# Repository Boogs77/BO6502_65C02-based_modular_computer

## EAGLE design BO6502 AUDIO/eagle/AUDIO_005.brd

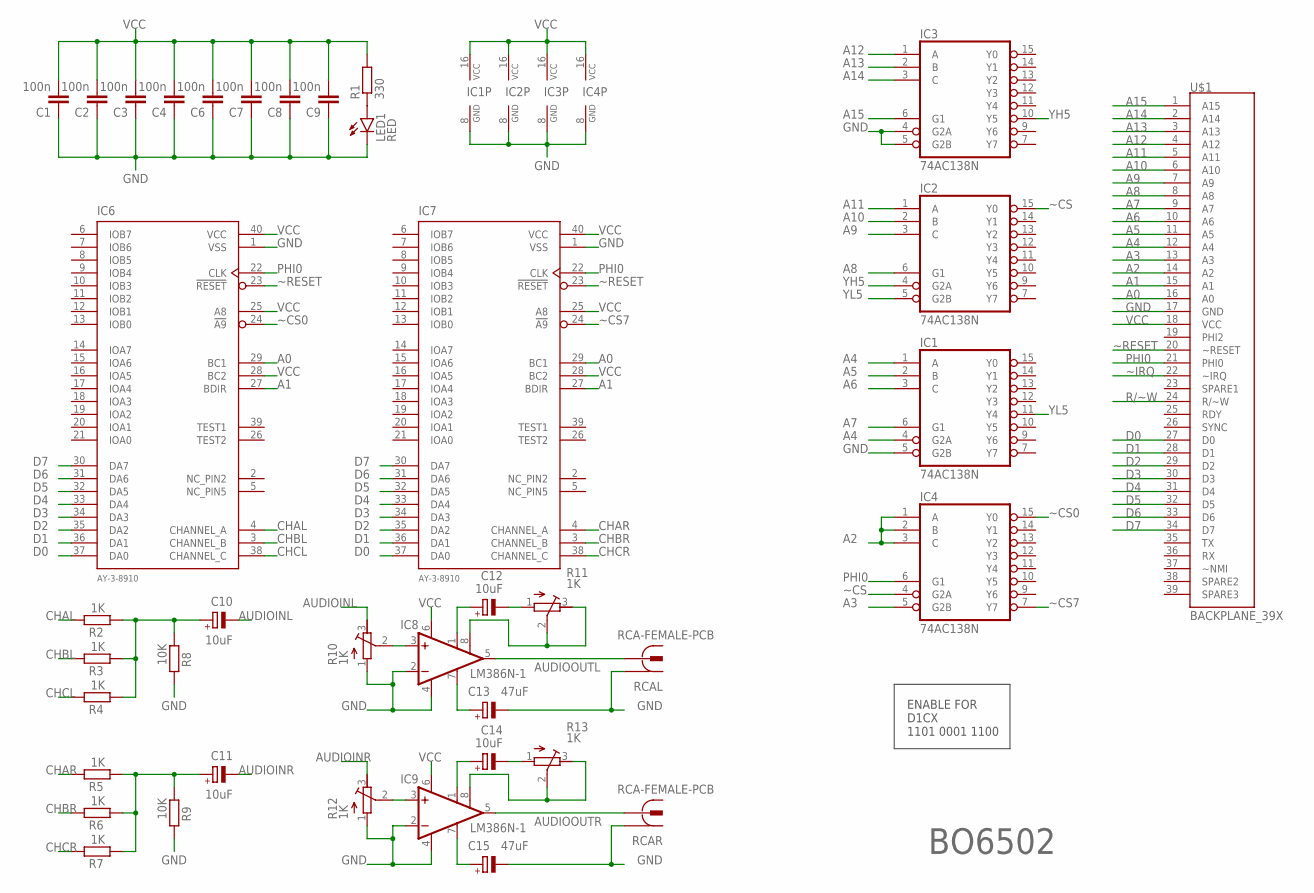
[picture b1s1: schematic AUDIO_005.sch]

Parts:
C1, C2, C3, C4, C6, C7, C8, C9: 100n; C025-025X050
C10, C11, C12, C14: 10uF; B45181A
C13, C15: 47uF; B45181A
IC1, IC2, IC3, IC4: 74AC138N; DIL16
IC6, IC7: AY-3-8910; DIL40
IC8, IC9: LM386N-1; DIL08
LED1: RED; LED5MM
R1: 330; 0207/10
R2, R3, R4, R5, R6, R7: 1K; 0207/10
R8, R9: 10K; 0207/10
R10, R11, R12, R13: 1K; RTRIM3339P
RCAL: RCA-FEMALE-PCB
RCAR: RCA-FEMALE-PCB
U$1: BACKPLANE_39X; BP_39X

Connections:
A0: IC6.29 (BC1), IC7.29 (BC1), U$1.16 (A0)
A1: IC6.27 (BDIR), IC7.27 (BDIR), U$1.15 (A1)
A2: IC4.1 (A), IC4.2 (B), IC4.3 (C), U$1.14 (A2)
A3: IC4.5 (G2B), U$1.13 (A3)
A4: IC1.1 (A), IC1.4 (G2A), U$1.12 (A4)
A5: IC1.2 (B), U$1.11 (A5)
A6: IC1.3 (C), U$1.10 (A6)
A7: IC1.6 (G1), U$1.9 (A7)
A8: IC2.6 (G1), U$1.8 (A8)
A9: IC2.3 (C), U$1.7 (A9)
A10: IC2.2 (B), U$1.6 (A10)
A11: IC2.1 (A), U$1.5 (A11)
A12: IC3.1 (A), U$1.4 (A12)
A13: IC3.2 (B), U$1.3 (A13)
A14: IC3.3 (C), U$1.2 (A14)
A15: IC3.6 (G1), U$1.1 (A15)
AUDIOINL: C10.-, R10.3 (E)
AUDIOINR: C11.-, R12.3 (E)
AUDIOOUTL: IC8.5 (OUT), RCAL.2@1 (2), RCAL.2@2 (2)
AUDIOOUTR: IC9.5 (OUT), RCAR.2@1 (2), RCAR.2@2 (2)
CHAL: IC6.4 (CHANNEL_A), R2.1
CHAR: IC7.4 (CHANNEL_A), R5.1
CHBL: IC6.3 (CHANNEL_B), R3.1
CHBR: IC7.3 (CHANNEL_B), R6.1
CHCL: IC6.38 (CHANNEL_C), R4.1
CHCR: IC7.38 (CHANNEL_C), R7.1
D0: IC6.37 (DA0), IC7.37 (DA0), U$1.27 (D0)
D1: IC6.36 (DA1), IC7.36 (DA1), U$1.28 (D1)
D2: IC6.35 (DA2), IC7.35 (DA2), U$1.29 (D2)
D3: IC6.34 (DA3), IC7.34 (DA3), U$1.30 (D3)
D4: IC6.33 (DA4), IC7.33 (DA4), U$1.31 (D4)
D5: IC6.32 (DA5), IC7.32 (DA5), U$1.32 (D5)
D6: IC6.31 (DA6), IC7.31 (DA6), U$1.33 (D6)
D7: IC6.30 (DA7), IC7.30 (DA7), U$1.34 (D7)
GND: C1.1, C2.1, C3.1, C4.1, C6.1, C7.1, C8.1, C9.1, C13.-, C15.-, IC1.5 (G2B), IC1.8 (GND), IC2.8 (GND), IC3.4 (G2A), IC3.5 (G2B), IC3.8 (GND), IC4.8 (GND), IC6.1 (VSS), IC7.1 (VSS), IC8.2 (-IN), IC8.4 (GND), IC9.2 (-IN), IC9.4 (GND), LED1.K (C), R8.1, R9.1, R10.1 (A), R12.1 (A), RCAL.1, RCAR.1, U$1.17 (GND)
unnamed: C10.+, R2.2, R3.2, R4.2, R8.2
unnamed: C12.+, IC8.1 (GAIN)
unnamed: IC8.3 (+IN), R10.2 (S)
unnamed: LED1.A, R1.1
unnamed: C12.-, R11.1 (A)
unnamed: IC8.8 (GAIN), R11.2 (S), R11.3 (E)
unnamed: C13.+, IC8.7 (BYPASS)
unnamed: IC9.3 (+IN), R12.2 (S)
unnamed: C14.+, IC9.1 (GAIN)
unnamed: C14.-, R13.1 (A)
unnamed: IC9.8 (GAIN), R13.2 (S), R13.3 (E)
unnamed: C15.+, IC9.7 (BYPASS)
unnamed: C11.+, R5.2, R6.2, R7.2, R9.2
PHI0: IC4.6 (G1), IC6.22 (CLK), IC7.22 (CLK), U$1.21 (PHI0)
R/~W: U$1.24 (R/~W)
VCC: C1.2, C2.2, C3.2, C4.2, C6.2, C7.2, C8.2, C9.2, IC1.16 (VCC), IC2.16 (VCC), IC3.16 (VCC), IC4.16 (VCC), IC6.25 (A8), IC6.28 (BC2), IC6.40 (VCC), IC7.25 (A8), IC7.28 (BC2), IC7.40 (VCC), IC8.6 (VS), IC9.6 (VS), R1.2, U$1.18 (VCC)
YH5: IC2.4 (G2A), IC3.10 (Y5)
YL5: IC1.11 (Y4), IC2.5 (G2B)
~CS: IC2.15 (Y0), IC4.4 (G2A)
~CS0: IC4.15 (Y0), IC6.24 (!A9)
~CS7: IC4.7 (Y7), IC7.24 (!A9)
~IRQ: U$1.22 (~IRQ)
~RESET: IC6.23 (!RESET), IC7.23 (!RESET), U$1.20 (~RESET)

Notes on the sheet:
BO6502
ENABLE FOR D1CX 1101 0001 1100

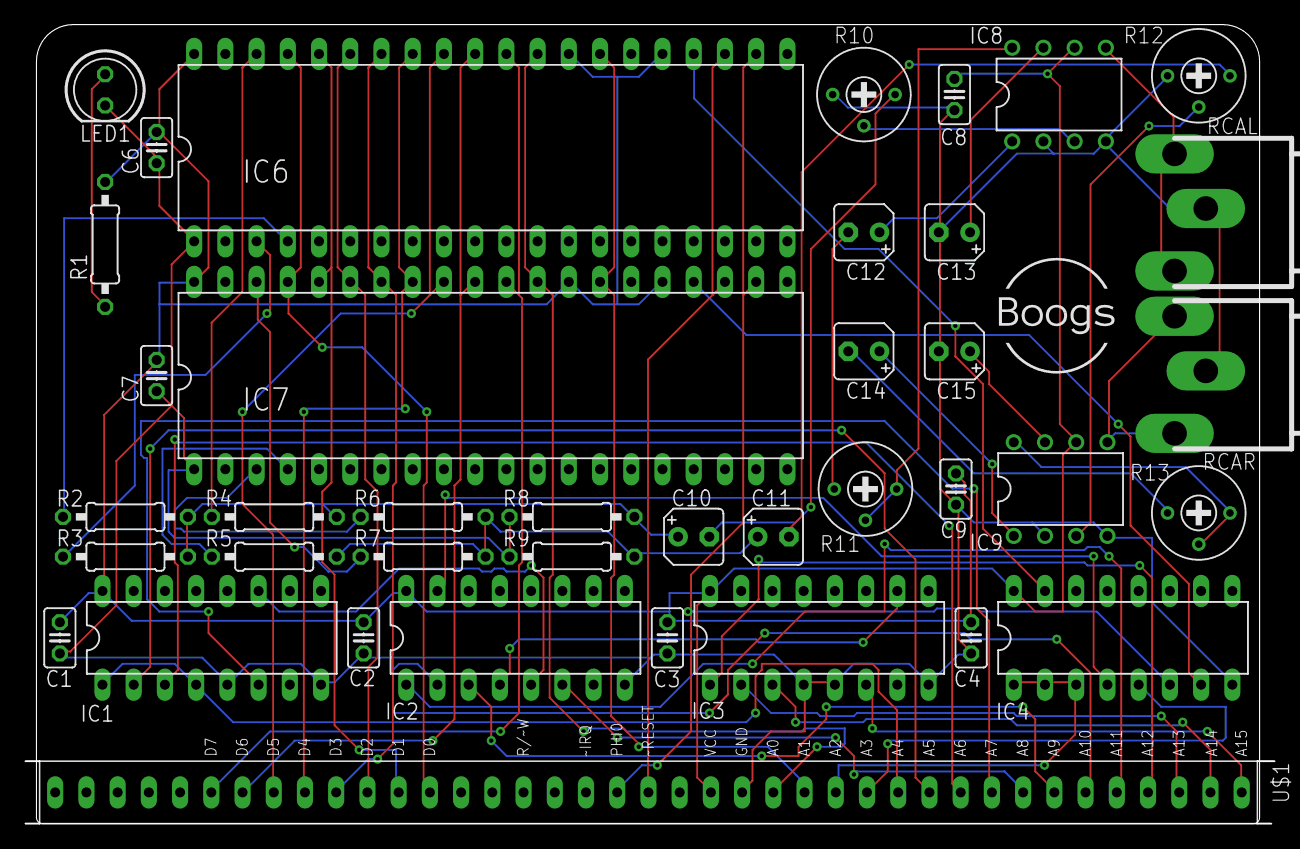
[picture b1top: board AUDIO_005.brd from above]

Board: 2 copper layers, 101.6 x 65.0 mm, 39 parts (0 on the bottom side), 56 nets.

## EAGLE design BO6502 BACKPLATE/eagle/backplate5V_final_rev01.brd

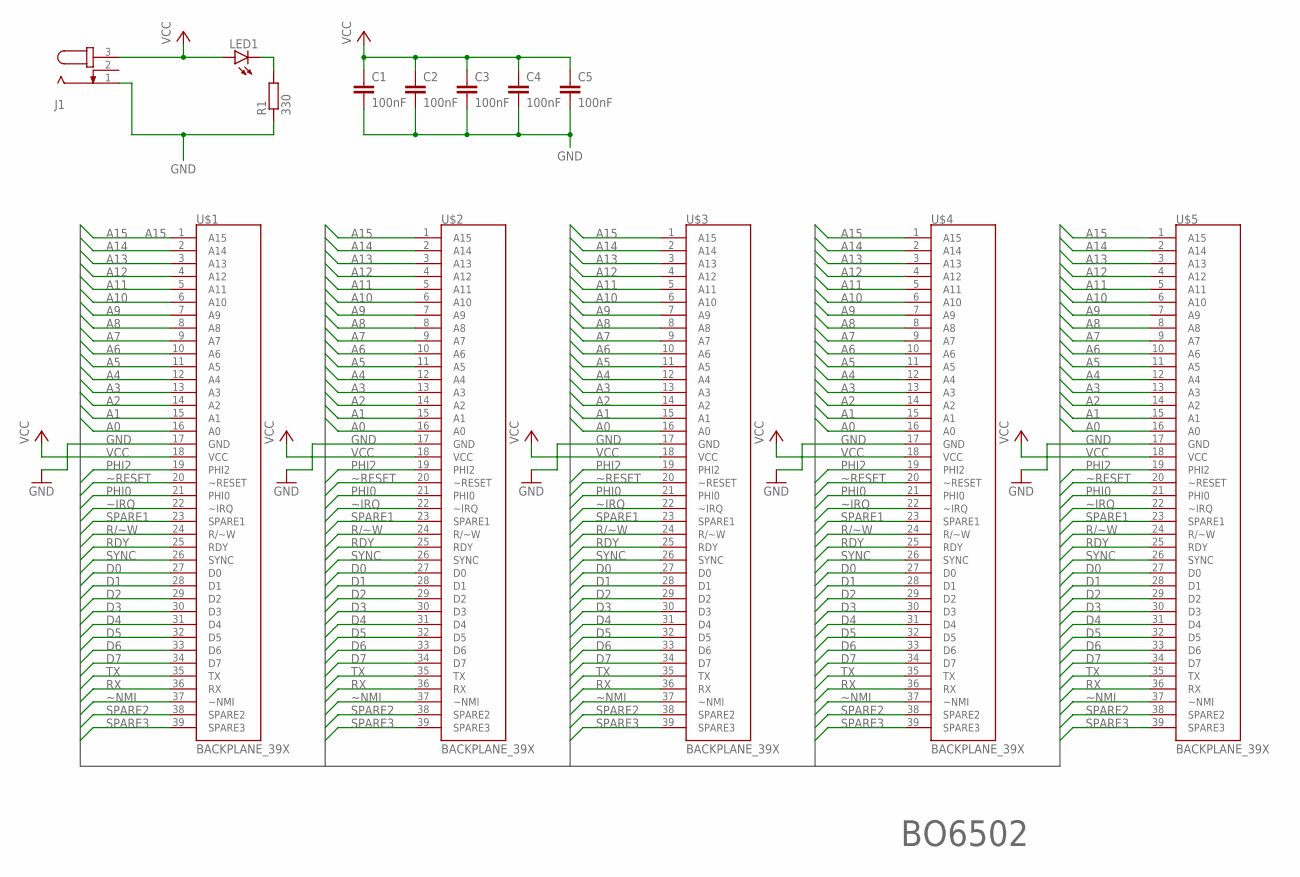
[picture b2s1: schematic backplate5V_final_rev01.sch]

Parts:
C1, C2, C3, C4, C5: 100nF; C025-025X050
J1: JACK-PLUG1; SPC4078
LED1: LED5MM
R1: 330; 0207/10
U$1, U$2, U$3, U$4, U$5: BACKPLANE_39X; BP_39X

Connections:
A0: U$1.16 (A0), U$2.16 (A0), U$3.16 (A0), U$4.16 (A0), U$5.16 (A0)
A1: U$1.15 (A1), U$2.15 (A1), U$3.15 (A1), U$4.15 (A1), U$5.15 (A1)
A2: U$1.14 (A2), U$2.14 (A2), U$3.14 (A2), U$4.14 (A2), U$5.14 (A2)
A3: U$1.13 (A3), U$2.13 (A3), U$3.13 (A3), U$4.13 (A3), U$5.13 (A3)
A4: U$1.12 (A4), U$2.12 (A4), U$3.12 (A4), U$4.12 (A4), U$5.12 (A4)
A5: U$1.11 (A5), U$2.11 (A5), U$3.11 (A5), U$4.11 (A5), U$5.11 (A5)
A6: U$1.10 (A6), U$2.10 (A6), U$3.10 (A6), U$4.10 (A6), U$5.10 (A6)
A7: U$1.9 (A7), U$2.9 (A7), U$3.9 (A7), U$4.9 (A7), U$5.9 (A7)
A8: U$1.8 (A8), U$2.8 (A8), U$3.8 (A8), U$4.8 (A8), U$5.8 (A8)
A9: U$1.7 (A9), U$2.7 (A9), U$3.7 (A9), U$4.7 (A9), U$5.7 (A9)
A10: U$1.6 (A10), U$2.6 (A10), U$3.6 (A10), U$4.6 (A10), U$5.6 (A10)
A11: U$1.5 (A11), U$2.5 (A11), U$3.5 (A11), U$4.5 (A11), U$5.5 (A11)
A12: U$1.4 (A12), U$2.4 (A12), U$3.4 (A12), U$4.4 (A12), U$5.4 (A12)
A13: U$1.3 (A13), U$2.3 (A13), U$3.3 (A13), U$4.3 (A13), U$5.3 (A13)
A14: U$1.2 (A14), U$2.2 (A14), U$3.2 (A14), U$4.2 (A14), U$5.2 (A14)
A15: U$1.1 (A15), U$2.1 (A15), U$3.1 (A15), U$4.1 (A15), U$5.1 (A15)
D0: U$1.27 (D0), U$2.27 (D0), U$3.27 (D0), U$4.27 (D0), U$5.27 (D0)
D1: U$1.28 (D1), U$2.28 (D1), U$3.28 (D1), U$4.28 (D1), U$5.28 (D1)
D2: U$1.29 (D2), U$2.29 (D2), U$3.29 (D2), U$4.29 (D2), U$5.29 (D2)
D3: U$1.30 (D3), U$2.30 (D3), U$3.30 (D3), U$4.30 (D3), U$5.30 (D3)
D4: U$1.31 (D4), U$2.31 (D4), U$3.31 (D4), U$4.31 (D4), U$5.31 (D4)
D5: U$1.32 (D5), U$2.32 (D5), U$3.32 (D5), U$4.32 (D5), U$5.32 (D5)
D6: U$1.33 (D6), U$2.33 (D6), U$3.33 (D6), U$4.33 (D6), U$5.33 (D6)
D7: U$1.34 (D7), U$2.34 (D7), U$3.34 (D7), U$4.34 (D7), U$5.34 (D7)
GND: C1.2, C2.2, C3.2, C4.2, C5.2, J1.1, R1.1, U$1.17 (GND), U$2.17 (GND), U$3.17 (GND), U$4.17 (GND), U$5.17 (GND)
unnamed: LED1.K (C), R1.2
PHI0: U$1.21 (PHI0), U$2.21 (PHI0), U$3.21 (PHI0), U$4.21 (PHI0), U$5.21 (PHI0)
PHI2: U$1.19 (PHI2), U$2.19 (PHI2), U$3.19 (PHI2), U$4.19 (PHI2), U$5.19 (PHI2)
R/~W: U$1.24 (R/~W), U$2.24 (R/~W), U$3.24 (R/~W), U$4.24 (R/~W), U$5.24 (R/~W)
RDY: U$1.25 (RDY), U$2.25 (RDY), U$3.25 (RDY), U$4.25 (RDY), U$5.25 (RDY)
RX: U$1.36 (RX), U$2.36 (RX), U$3.36 (RX), U$4.36 (RX), U$5.36 (RX)
SPARE1: U$1.23 (SPARE1), U$2.23 (SPARE1), U$3.23 (SPARE1), U$4.23 (SPARE1), U$5.23 (SPARE1)
SPARE2: U$1.38 (SPARE2), U$2.38 (SPARE2), U$3.38 (SPARE2), U$4.38 (SPARE2), U$5.38 (SPARE2)
SPARE3: U$1.39 (SPARE3), U$2.39 (SPARE3), U$3.39 (SPARE3), U$4.39 (SPARE3), U$5.39 (SPARE3)
SYNC: U$1.26 (SYNC), U$2.26 (SYNC), U$3.26 (SYNC), U$4.26 (SYNC), U$5.26 (SYNC)
TX: U$1.35 (TX), U$2.35 (TX), U$3.35 (TX), U$4.35 (TX), U$5.35 (TX)
VCC: C1.1, C2.1, C3.1, C4.1, C5.1, J1.3, LED1.A, U$1.18 (VCC), U$2.18 (VCC), U$3.18 (VCC), U$4.18 (VCC), U$5.18 (VCC)
~IRQ: U$1.22 (~IRQ), U$2.22 (~IRQ), U$3.22 (~IRQ), U$4.22 (~IRQ), U$5.22 (~IRQ)
~NMI: U$1.37 (~NMI), U$2.37 (~NMI), U$3.37 (~NMI), U$4.37 (~NMI), U$5.37 (~NMI)
~RESET: U$1.20 (~RESET), U$2.20 (~RESET), U$3.20 (~RESET), U$4.20 (~RESET), U$5.20 (~RESET)

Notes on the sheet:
BO6502

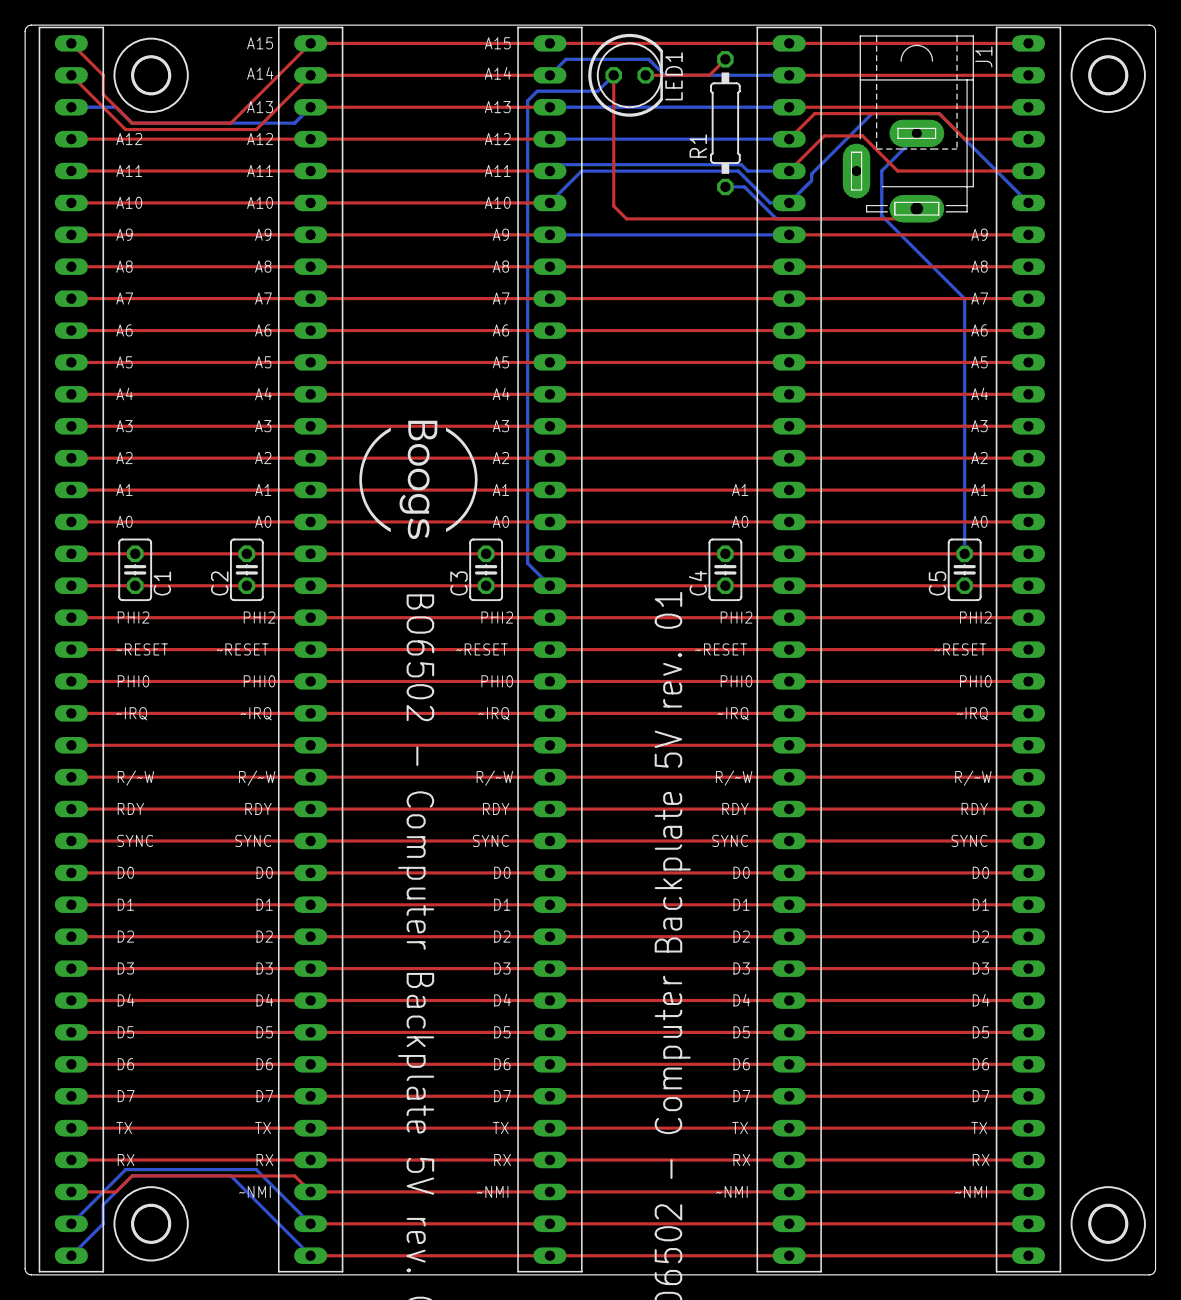
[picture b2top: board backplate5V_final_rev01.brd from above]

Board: 2 copper layers, 90.0 x 99.5 mm, 17 parts (0 on the bottom side), 40 nets.

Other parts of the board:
U$7, U$8, U$9, U$10: 2,8

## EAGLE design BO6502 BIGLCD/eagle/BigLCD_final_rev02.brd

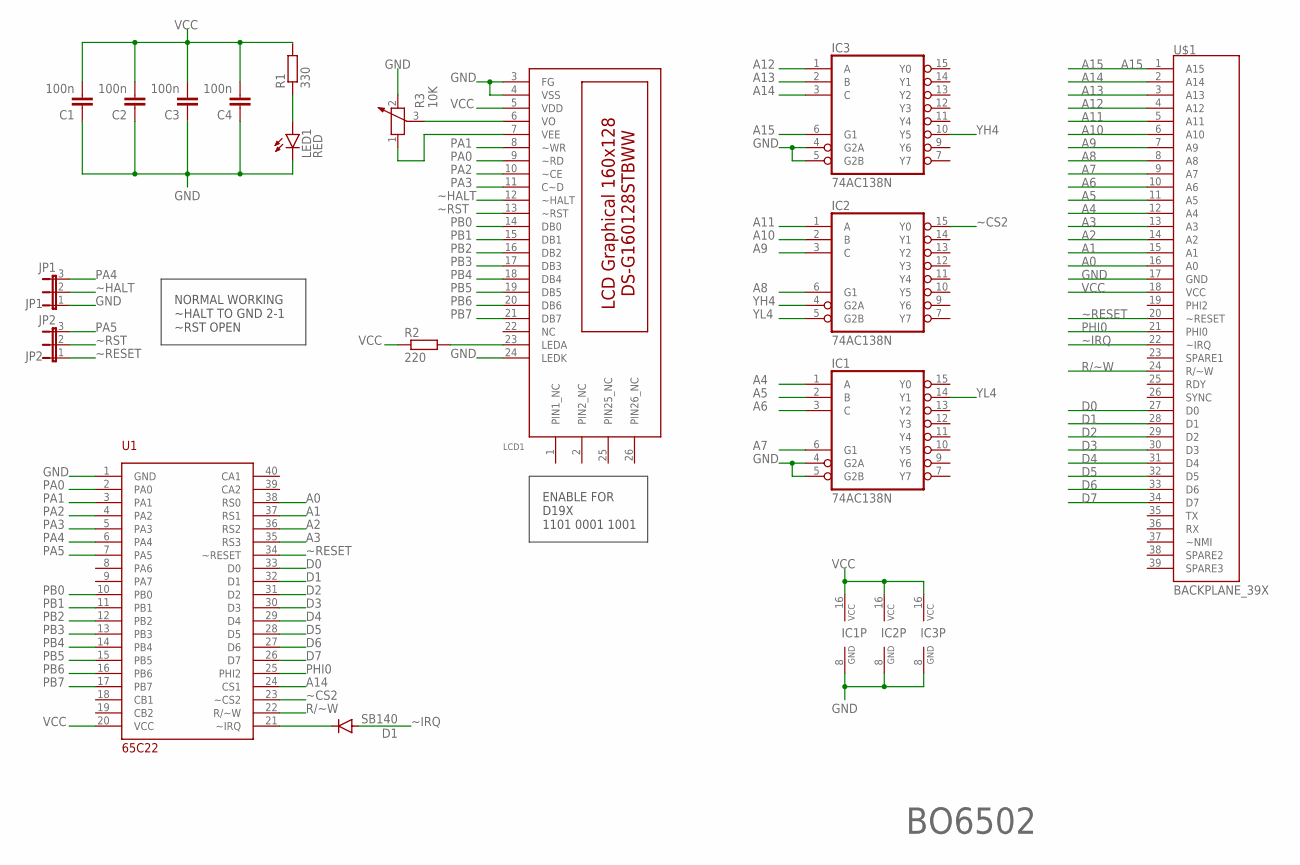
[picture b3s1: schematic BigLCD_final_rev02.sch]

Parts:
C1, C2, C3, C4: 100n; C025-025X050
D1: SB140; DO41-10
IC1, IC2, IC3: 74AC138N; DIL16
JP1: JP1; JP2
JP2: JP2
LCD1: DS-G160128STBWW; PAK100/2500-26
LED1: RED; LED5MM
R1: 330; 0207/10
R2: 220; 0207/10
R3: 10K; PT-10
U1: 65C22; DIL40
U$1: BACKPLANE_39X; BP_39X

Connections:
A0: U1.38 (RS0), U$1.16 (A0)
A1: U1.37 (RS1), U$1.15 (A1)
A2: U1.36 (RS2), U$1.14 (A2)
A3: U1.35 (RS3), U$1.13 (A3)
A4: IC1.1 (A), U$1.12 (A4)
A5: IC1.2 (B), U$1.11 (A5)
A6: IC1.3 (C), U$1.10 (A6)
A7: IC1.6 (G1), U$1.9 (A7)
A8: IC2.6 (G1), U$1.8 (A8)
A9: IC2.3 (C), U$1.7 (A9)
A10: IC2.2 (B), U$1.6 (A10)
A11: IC2.1 (A), U$1.5 (A11)
A12: IC3.1 (A), U$1.4 (A12)
A13: IC3.2 (B), U$1.3 (A13)
A14: IC3.3 (C), U1.24 (CS1), U$1.2 (A14)
A15: IC3.6 (G1), U$1.1 (A15)
D0: U1.33 (D0), U$1.27 (D0)
D1: U1.32 (D1), U$1.28 (D1)
D2: U1.31 (D2), U$1.29 (D2)
D3: U1.30 (D3), U$1.30 (D3)
D4: U1.29 (D4), U$1.31 (D4)
D5: U1.28 (D5), U$1.32 (D5)
D6: U1.27 (D6), U$1.33 (D6)
D7: U1.26 (D7), U$1.34 (D7)
GND: C1.1, C2.1, C3.1, C4.1, IC1.4 (G2A), IC1.5 (G2B), IC1.8 (GND), IC2.8 (GND), IC3.4 (G2A), IC3.5 (G2B), IC3.8 (GND), JP1.1, LCD1.3 (FG), LCD1.4 (VSS), LCD1.24 (LEDK), LED1.K (C), R3.2, U1.1 (GND), U$1.17 (GND)
unnamed: D1.C, U1.21 (~IRQ)
unnamed: LCD1.6 (VO), R3.3
unnamed: LCD1.7 (VEE), R3.1
unnamed: LCD1.23 (LEDA), R2.2
unnamed: LED1.A, R1.1
PA0: LCD1.9 (~RD), U1.2 (PA0)
PA1: LCD1.8 (~WR), U1.3 (PA1)
PA2: LCD1.10 (~CE), U1.4 (PA2)
PA3: LCD1.11 (C~D), U1.5 (PA3)
PA4: JP1.3, U1.6 (PA4)
PA5: JP2.3, U1.7 (PA5)
PB0: LCD1.14 (DB0), U1.10 (PB0)
PB1: LCD1.15 (DB1), U1.11 (PB1)
PB2: LCD1.16 (DB2), U1.12 (PB2)
PB3: LCD1.17 (DB3), U1.13 (PB3)
PB4: LCD1.18 (DB4), U1.14 (PB4)
PB5: LCD1.19 (DB5), U1.15 (PB5)
PB6: LCD1.20 (DB6), U1.16 (PB6)
PB7: LCD1.21 (DB7), U1.17 (PB7)
PHI0: U1.25 (PHI2), U$1.21 (PHI0)
R/~W: U1.22 (R/~W), U$1.24 (R/~W)
VCC: C1.2, C2.2, C3.2, C4.2, IC1.16 (VCC), IC2.16 (VCC), IC3.16 (VCC), LCD1.5 (VDD), R1.2, R2.1, U1.20 (VCC), U$1.18 (VCC)
YH4: IC2.4 (G2A), IC3.10 (Y5)
YL4: IC1.14 (Y1), IC2.5 (G2B)
~CS2: IC2.15 (Y0), U1.23 (~CS2)
~HALT: JP1.2, LCD1.12 (~HALT)
~IRQ: D1.A, U$1.22 (~IRQ)
~RESET: JP2.1, U1.34 (~RESET), U$1.20 (~RESET)
~RST: JP2.2, LCD1.13 (~RST)

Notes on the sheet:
BO6502
ENABLE FOR D19X 1101 0001 1001
NORMAL WORKING ~HALT TO GND 2-1 ~RST OPEN

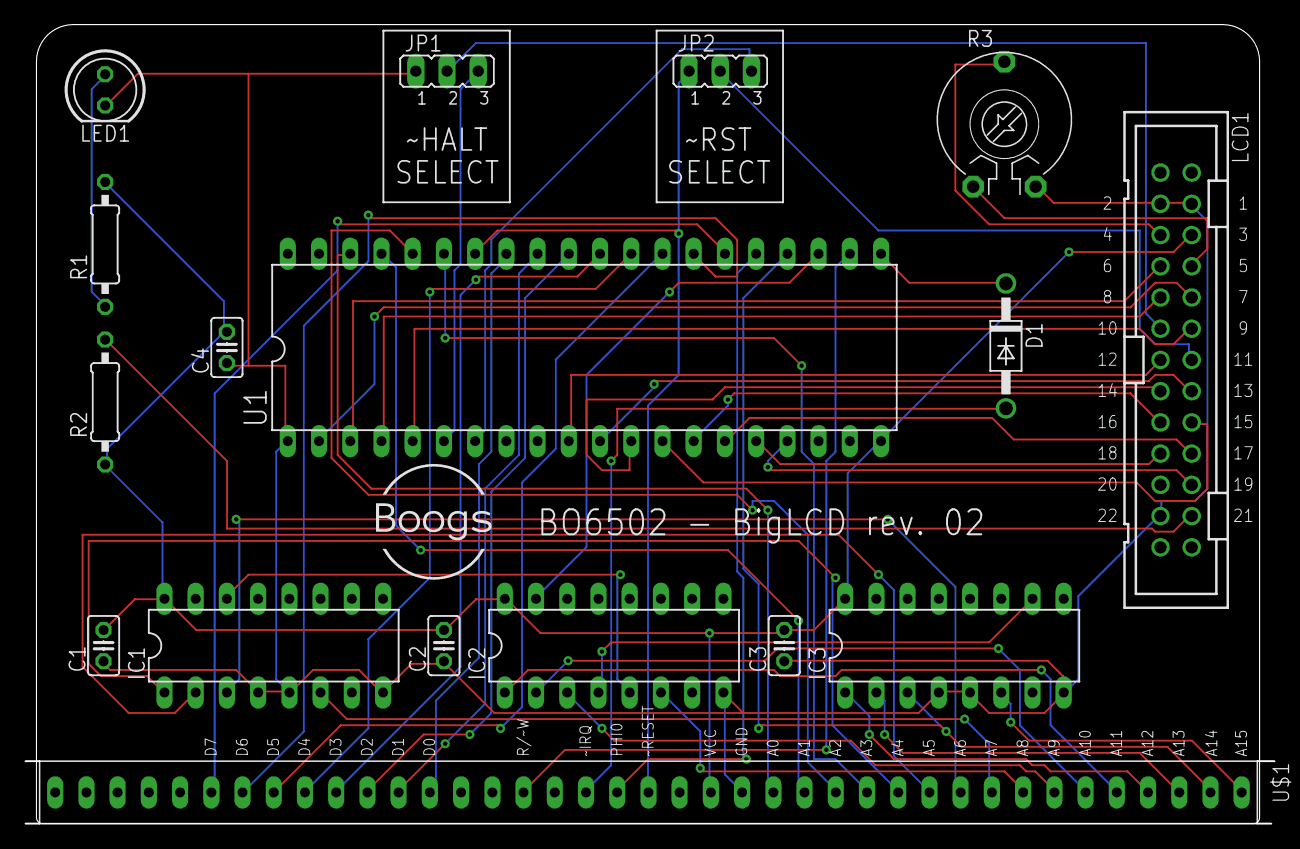
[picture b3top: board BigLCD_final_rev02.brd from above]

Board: 2 copper layers, 101.6 x 65.0 mm, 17 parts (0 on the bottom side), 54 nets.

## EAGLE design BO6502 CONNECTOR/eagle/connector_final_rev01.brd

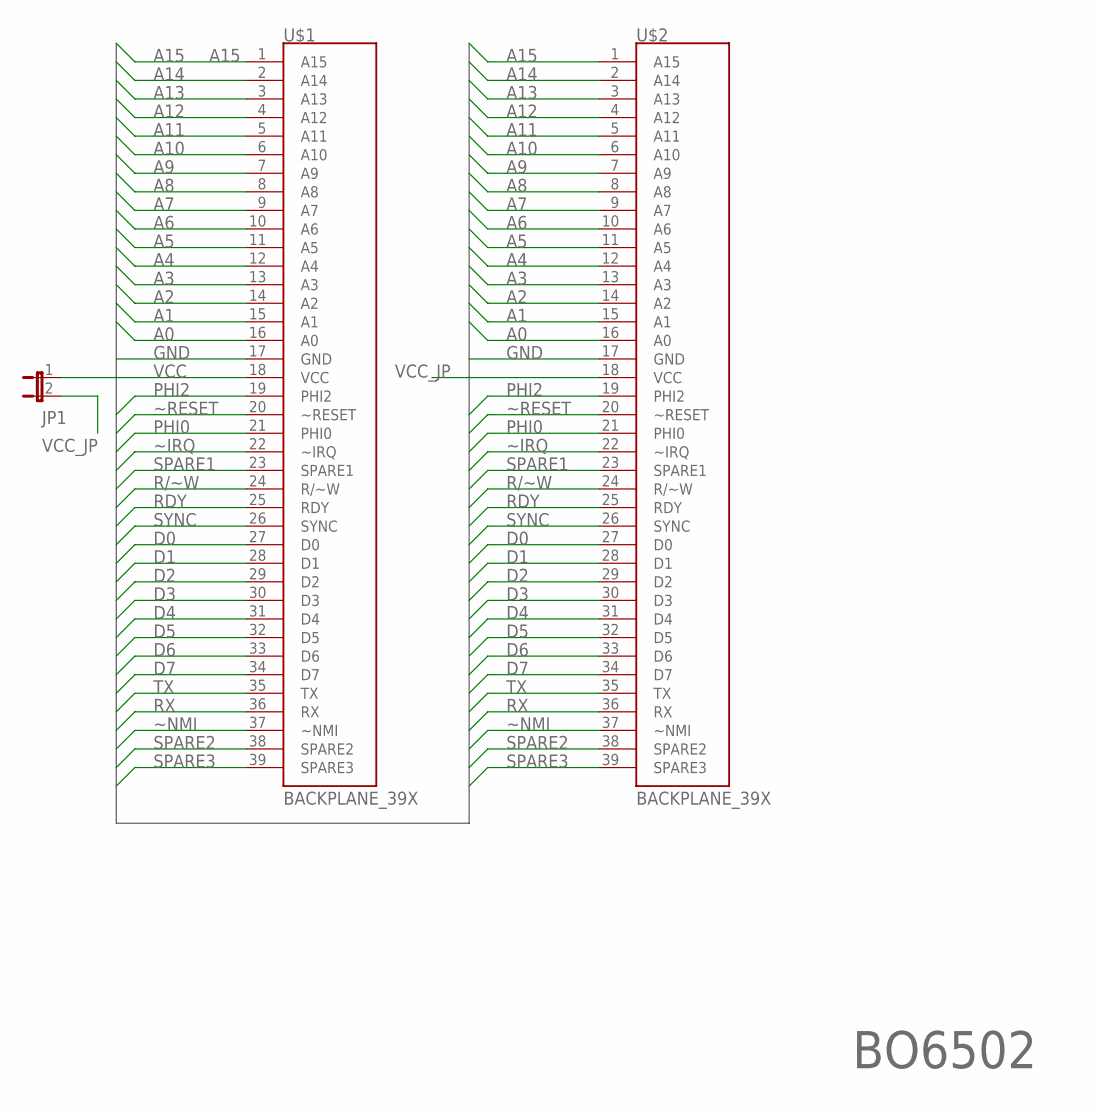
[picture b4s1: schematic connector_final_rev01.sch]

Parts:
JP1: JP1E; JP1
U$1, U$2: BACKPLANE_39X; BP_39X

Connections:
A0: U$1.16 (A0), U$2.16 (A0)
A1: U$1.15 (A1), U$2.15 (A1)
A2: U$1.14 (A2), U$2.14 (A2)
A3: U$1.13 (A3), U$2.13 (A3)
A4: U$1.12 (A4), U$2.12 (A4)
A5: U$1.11 (A5), U$2.11 (A5)
A6: U$1.10 (A6), U$2.10 (A6)
A7: U$1.9 (A7), U$2.9 (A7)
A8: U$1.8 (A8), U$2.8 (A8)
A9: U$1.7 (A9), U$2.7 (A9)
A10: U$1.6 (A10), U$2.6 (A10)
A11: U$1.5 (A11), U$2.5 (A11)
A12: U$1.4 (A12), U$2.4 (A12)
A13: U$1.3 (A13), U$2.3 (A13)
A14: U$1.2 (A14), U$2.2 (A14)
A15: U$1.1 (A15), U$2.1 (A15)
D0: U$1.27 (D0), U$2.27 (D0)
D1: U$1.28 (D1), U$2.28 (D1)
D2: U$1.29 (D2), U$2.29 (D2)
D3: U$1.30 (D3), U$2.30 (D3)
D4: U$1.31 (D4), U$2.31 (D4)
D5: U$1.32 (D5), U$2.32 (D5)
D6: U$1.33 (D6), U$2.33 (D6)
D7: U$1.34 (D7), U$2.34 (D7)
GND: U$1.17 (GND), U$2.17 (GND)
PHI0: U$1.21 (PHI0), U$2.21 (PHI0)
PHI2: U$1.19 (PHI2), U$2.19 (PHI2)
R/~W: U$1.24 (R/~W), U$2.24 (R/~W)
RDY: U$1.25 (RDY), U$2.25 (RDY)
RX: U$1.36 (RX), U$2.36 (RX)
SPARE1: U$1.23 (SPARE1), U$2.23 (SPARE1)
SPARE2: U$1.38 (SPARE2), U$2.38 (SPARE2)
SPARE3: U$1.39 (SPARE3), U$2.39 (SPARE3)
SYNC: U$1.26 (SYNC), U$2.26 (SYNC)
TX: U$1.35 (TX), U$2.35 (TX)
VCC: JP1.1, U$1.18 (VCC)
VCC_JP: JP1.2, U$2.18 (VCC)
~IRQ: U$1.22 (~IRQ), U$2.22 (~IRQ)
~NMI: U$1.37 (~NMI), U$2.37 (~NMI)
~RESET: U$1.20 (~RESET), U$2.20 (~RESET)

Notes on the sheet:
BO6502

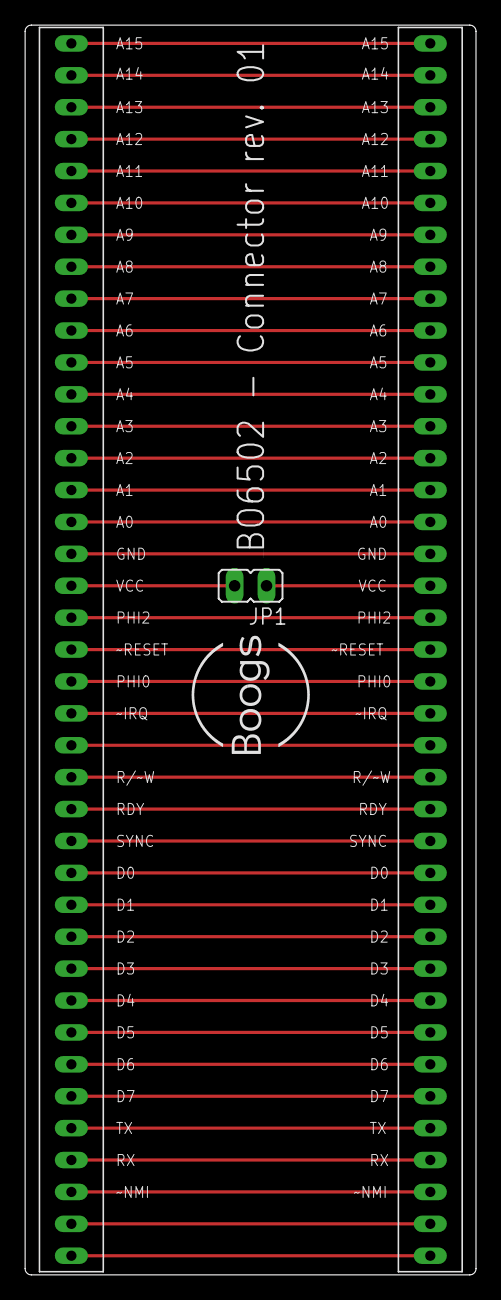
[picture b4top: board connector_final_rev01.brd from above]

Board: 2 copper layers, 35.9 x 99.5 mm, 3 parts (0 on the bottom side), 40 nets.

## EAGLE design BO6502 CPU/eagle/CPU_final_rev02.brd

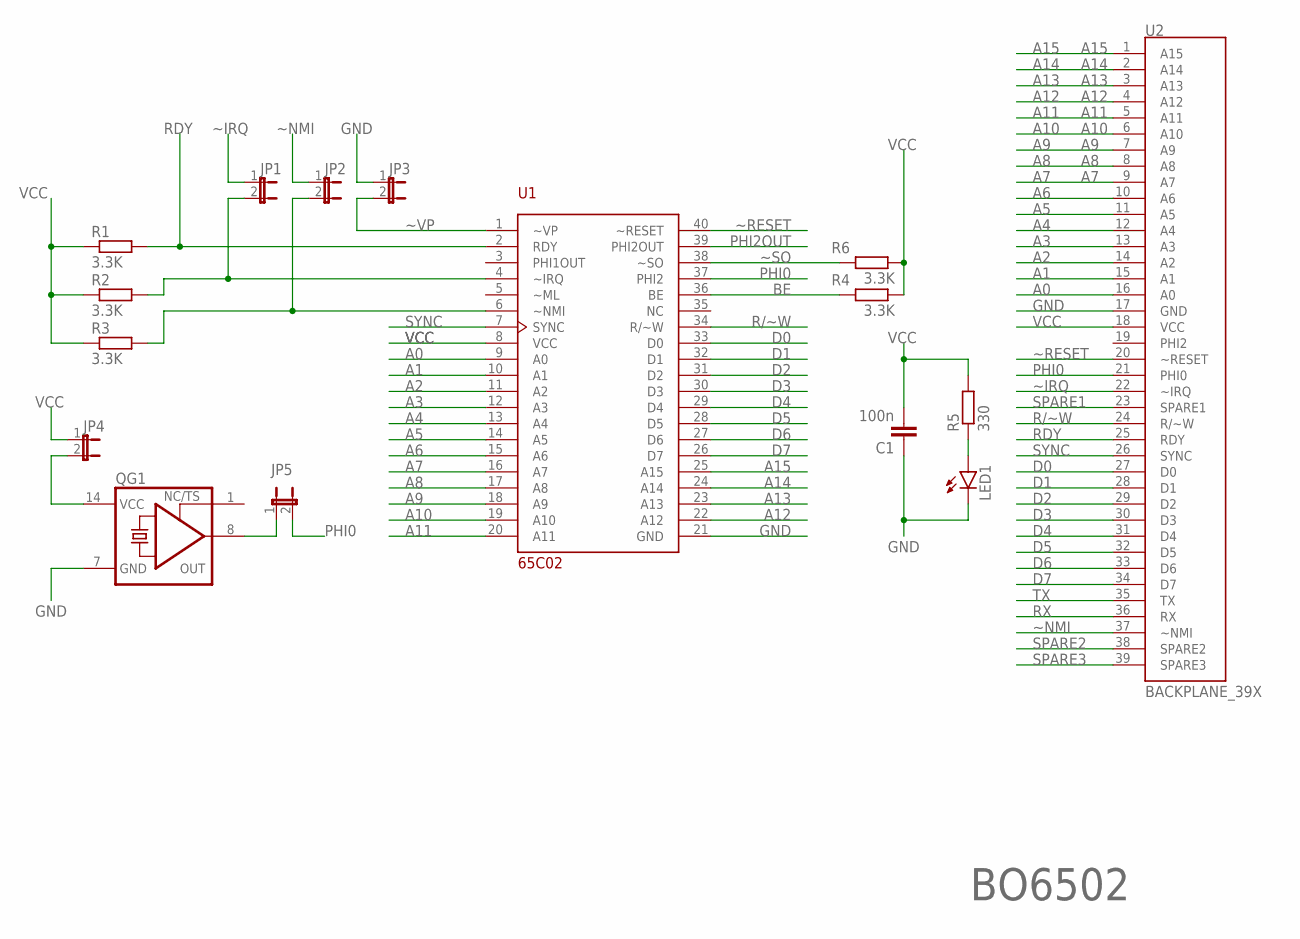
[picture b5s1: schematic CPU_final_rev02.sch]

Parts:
C1: 100n; C025-025X050
JP1, JP2, JP3, JP4, JP5: JP1E; JP1
LED1: LED5MM
QG1: XO-14; DIL14S
R1, R2, R3, R4, R6: 3.3K; 0207/10
R5: 330; 0207/10
U1: 65C02; DIL40
U2: BACKPLANE_39X; BP_39X

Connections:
A0: U1.9 (A0), U2.16 (A0)
A1: U1.10 (A1), U2.15 (A1)
A2: U1.11 (A2), U2.14 (A2)
A3: U1.12 (A3), U2.13 (A3)
A4: U1.13 (A4), U2.12 (A4)
A5: U1.14 (A5), U2.11 (A5)
A6: U1.15 (A6), U2.10 (A6)
A7: U1.16 (A7), U2.9 (A7)
A8: U1.17 (A8), U2.8 (A8)
A9: U1.18 (A9), U2.7 (A9)
A10: U1.19 (A10), U2.6 (A10)
A11: U1.20 (A11), U2.5 (A11)
A12: U1.22 (A12), U2.4 (A12)
A13: U1.23 (A13), U2.3 (A13)
A14: U1.24 (A14), U2.2 (A14)
A15: U1.25 (A15), U2.1 (A15)
BE: R4.1, U1.36 (BE)
D0: U1.33 (D0), U2.27 (D0)
D1: U1.32 (D1), U2.28 (D1)
D2: U1.31 (D2), U2.29 (D2)
D3: U1.30 (D3), U2.30 (D3)
D4: U1.29 (D4), U2.31 (D4)
D5: U1.28 (D5), U2.32 (D5)
D6: U1.27 (D6), U2.33 (D6)
D7: U1.26 (D7), U2.34 (D7)
GND: C1.1, JP3.1, LED1.K (C), QG1.7 (GND), U1.21 (GND), U2.17 (GND)
unnamed: JP4.2, QG1.14 (VCC)
unnamed: JP1.2, R2.2, U1.4 (~IRQ)
unnamed: JP2.2, R3.2, U1.6 (~NMI)
unnamed: JP5.1, QG1.8 (OUT)
unnamed: LED1.A, R5.1
PHI0: JP5.2, U1.37 (PHI2), U2.21 (PHI0)
PHI2OUT: U1.39 (PHI2OUT)
R/~W: U1.34 (R/~W), U2.24 (R/~W)
RDY: R1.2, U1.2 (RDY), U2.25 (RDY)
RX: U2.36 (RX)
SPARE1: U2.23 (SPARE1)
SPARE2: U2.38 (SPARE2)
SPARE3: U2.39 (SPARE3)
SYNC: U1.7 (SYNC), U2.26 (SYNC)
TX: U2.35 (TX)
VCC: C1.2, JP4.1, R1.1, R2.1, R3.1, R4.2, R5.2, R6.2, U1.8 (VCC), U2.18 (VCC)
~IRQ: JP1.1, U2.22 (~IRQ)
~NMI: JP2.1, U2.37 (~NMI)
~RESET: U1.40 (~RESET), U2.20 (~RESET)
~SO: R6.1, U1.38 (~SO)
~VP: JP3.2, U1.1 (~VP)

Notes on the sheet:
BO6502

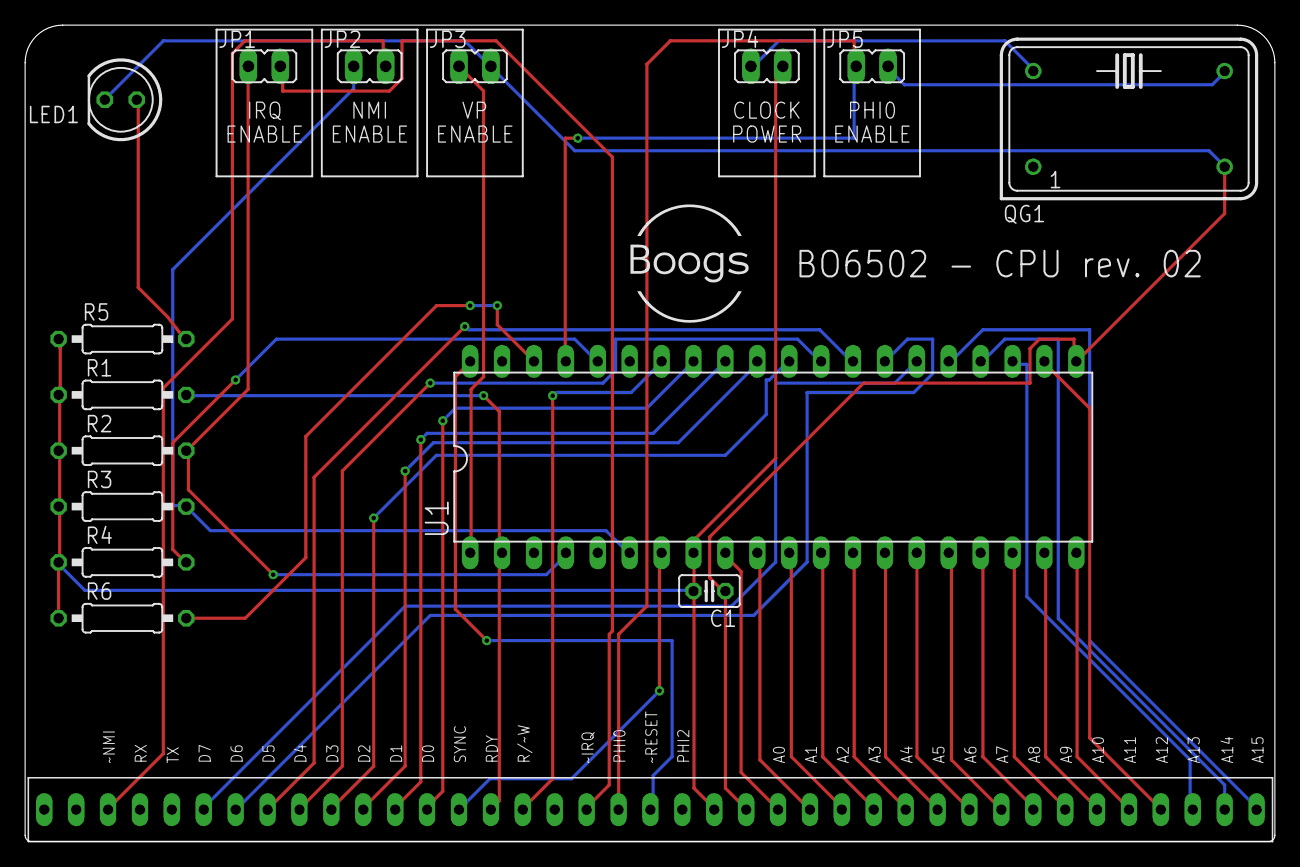
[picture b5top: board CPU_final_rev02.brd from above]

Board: 2 copper layers, 99.5 x 65.0 mm, 16 parts (0 on the bottom side), 41 nets.

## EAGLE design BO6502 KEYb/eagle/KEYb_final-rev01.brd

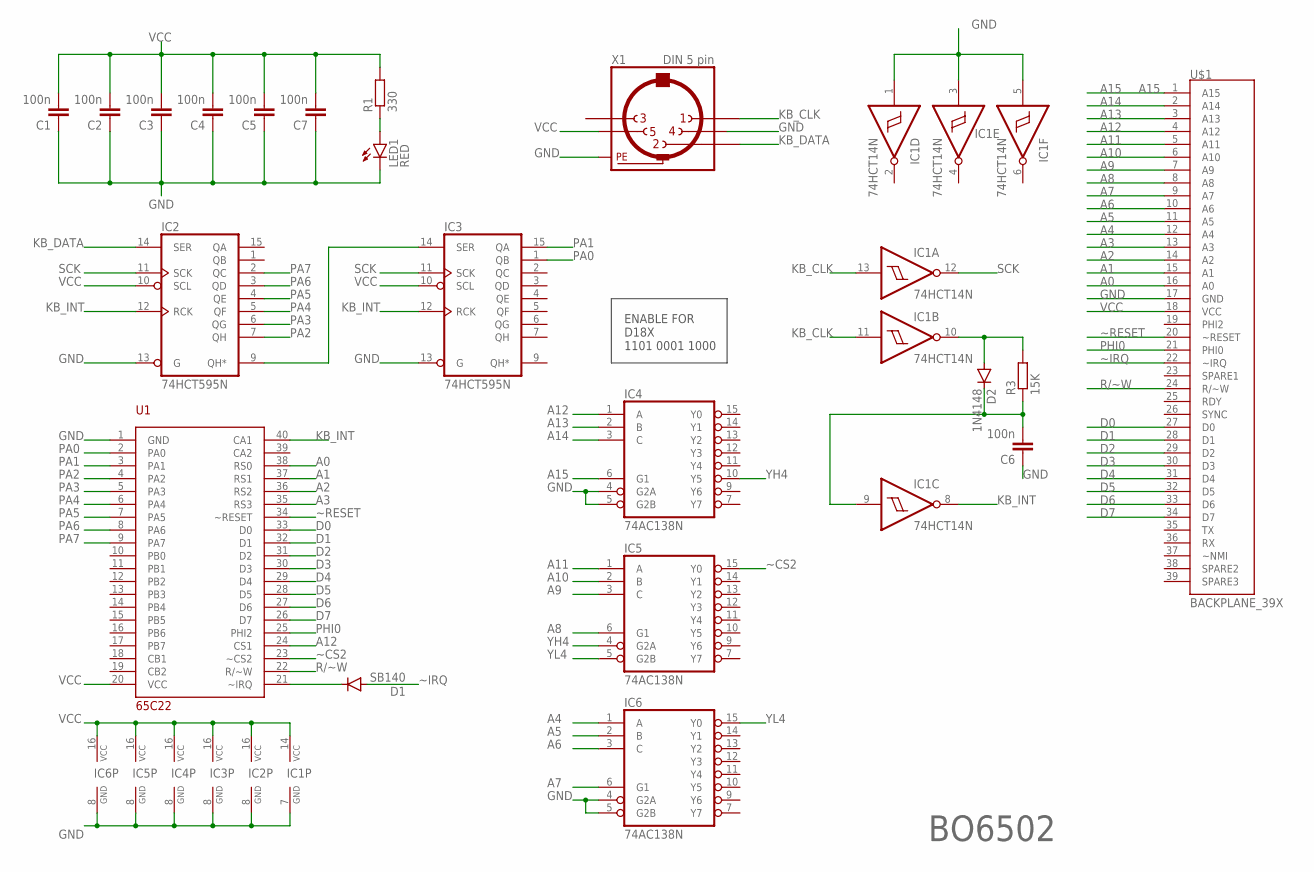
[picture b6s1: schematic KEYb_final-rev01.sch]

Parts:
C1, C2, C3, C4, C5, C6, C7: 100n; C025-025X050
D1: SB140; DO41-10
D2: 1N4148; DO35-7
IC1: 74HCT14N; DIL14
IC2, IC3: 74HCT595N; DIL16
IC4, IC5, IC6: 74AC138N; DIL16
LED1: RED; LED5MM
R1: 330; 0207/10
R3: 15K; 0207/10
U1: 65C22; DIL40
U$1: BACKPLANE_39X; BP_39X
X1: DIN 5 pin; MAB5SH

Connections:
A0: U1.38 (RS0), U$1.16 (A0)
A1: U1.37 (RS1), U$1.15 (A1)
A2: U1.36 (RS2), U$1.14 (A2)
A3: U1.35 (RS3), U$1.13 (A3)
A4: IC6.1 (A), U$1.12 (A4)
A5: IC6.2 (B), U$1.11 (A5)
A6: IC6.3 (C), U$1.10 (A6)
A7: IC6.6 (G1), U$1.9 (A7)
A8: IC5.6 (G1), U$1.8 (A8)
A9: IC5.3 (C), U$1.7 (A9)
A10: IC5.2 (B), U$1.6 (A10)
A11: IC5.1 (A), U$1.5 (A11)
A12: IC4.1 (A), U1.24 (CS1), U$1.4 (A12)
A13: IC4.2 (B), U$1.3 (A13)
A14: IC4.3 (C), U$1.2 (A14)
A15: IC4.6 (G1), U$1.1 (A15)
D0: U1.33 (D0), U$1.27 (D0)
D1: U1.32 (D1), U$1.28 (D1)
D2: U1.31 (D2), U$1.29 (D2)
D3: U1.30 (D3), U$1.30 (D3)
D4: U1.29 (D4), U$1.31 (D4)
D5: U1.28 (D5), U$1.32 (D5)
D6: U1.27 (D6), U$1.33 (D6)
D7: U1.26 (D7), U$1.34 (D7)
GND: C1.1, C2.1, C3.1, C4.1, C5.1, C6.1, C7.1, IC1.1 (I), IC1.3 (I), IC1.5 (I), IC1.7 (GND), IC2.8 (GND), IC2.13 (G), IC3.8 (GND), IC3.13 (G), IC4.4 (G2A), IC4.5 (G2B), IC4.8 (GND), IC5.8 (GND), IC6.4 (G2A), IC6.5 (G2B), IC6.8 (GND), LED1.K (C), U1.1 (GND), U$1.17 (GND), X1.4, X1.PE, X1.PE@ (PE)
KB_CLK: IC1.11 (I), IC1.13 (I), X1.1
KB_DATA: IC2.14 (SER), X1.2
KB_INT: IC1.8 (O), IC2.12 (RCK), IC3.12 (RCK), U1.40 (CA1)
unnamed: D1.C, U1.21 (~IRQ)
unnamed: IC2.9 (QH*), IC3.14 (SER)
unnamed: D2.A, IC1.10 (O), R3.2
unnamed: C6.2, D2.C, IC1.9 (I), R3.1
unnamed: LED1.A, R1.1
PA0: IC3.1 (QB), U1.2 (PA0)
PA1: IC3.15 (QA), U1.3 (PA1)
PA2: IC2.7 (QH), U1.4 (PA2)
PA3: IC2.6 (QG), U1.5 (PA3)
PA4: IC2.5 (QF), U1.6 (PA4)
PA5: IC2.4 (QE), U1.7 (PA5)
PA6: IC2.3 (QD), U1.8 (PA6)
PA7: IC2.2 (QC), U1.9 (PA7)
PHI0: U1.25 (PHI2), U$1.21 (PHI0)
R/~W: U1.22 (R/~W), U$1.24 (R/~W)
SCK: IC1.12 (O), IC2.11 (SCK), IC3.11 (SCK)
VCC: C1.2, C2.2, C3.2, C4.2, C5.2, C7.2, IC1.14 (VCC), IC2.10 (SCL), IC2.16 (VCC), IC3.10 (SCL), IC3.16 (VCC), IC4.16 (VCC), IC5.16 (VCC), IC6.16 (VCC), R1.2, U1.20 (VCC), U$1.18 (VCC), X1.5
YH4: IC4.10 (Y5), IC5.4 (G2A)
YL4: IC5.5 (G2B), IC6.15 (Y0)
~CS2: IC5.15 (Y0), U1.23 (~CS2)
~IRQ: D1.A, U$1.22 (~IRQ)
~RESET: U1.34 (~RESET), U$1.20 (~RESET)

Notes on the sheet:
BO6502
ENABLE FOR D18X 1101 0001 1000

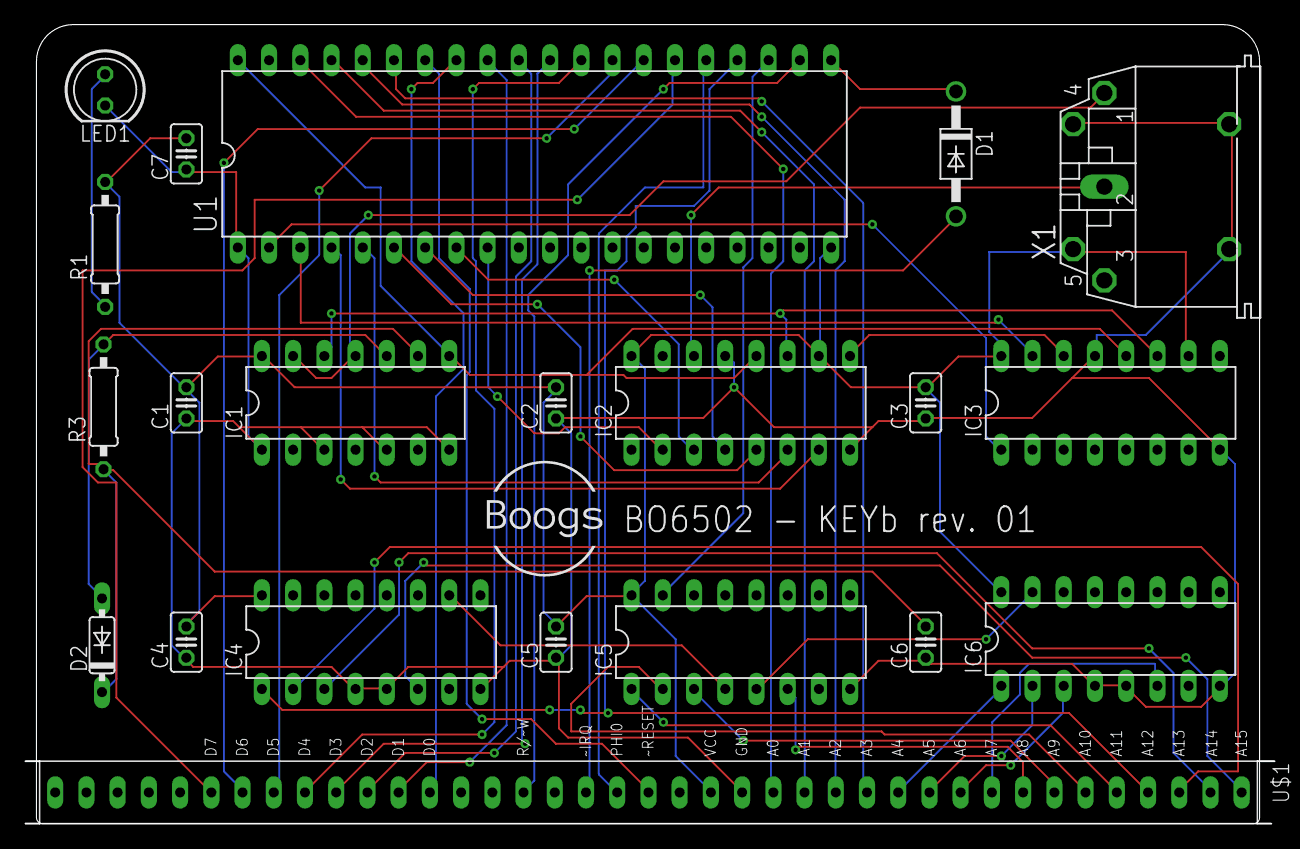
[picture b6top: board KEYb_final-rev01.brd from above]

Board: 2 copper layers, 101.6 x 65.0 mm, 21 parts (0 on the bottom side), 50 nets.
